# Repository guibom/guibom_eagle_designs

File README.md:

Miscellaneous OSH Stuff
====================

Misc breakouts, boards and parts for Cad Eagle.
All OSH with the MIT license.

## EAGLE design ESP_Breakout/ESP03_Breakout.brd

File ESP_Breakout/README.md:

ESP8266 module 01 & 03 Breakout
====================

Simple breakout for either module 01 (dip dual-header) or 03 (smd with ceramic antenna). Works fine on a breadboard (but it takes up some space).
Breaks out the GPIOs, and RST is tied to the GPIO16 pin.

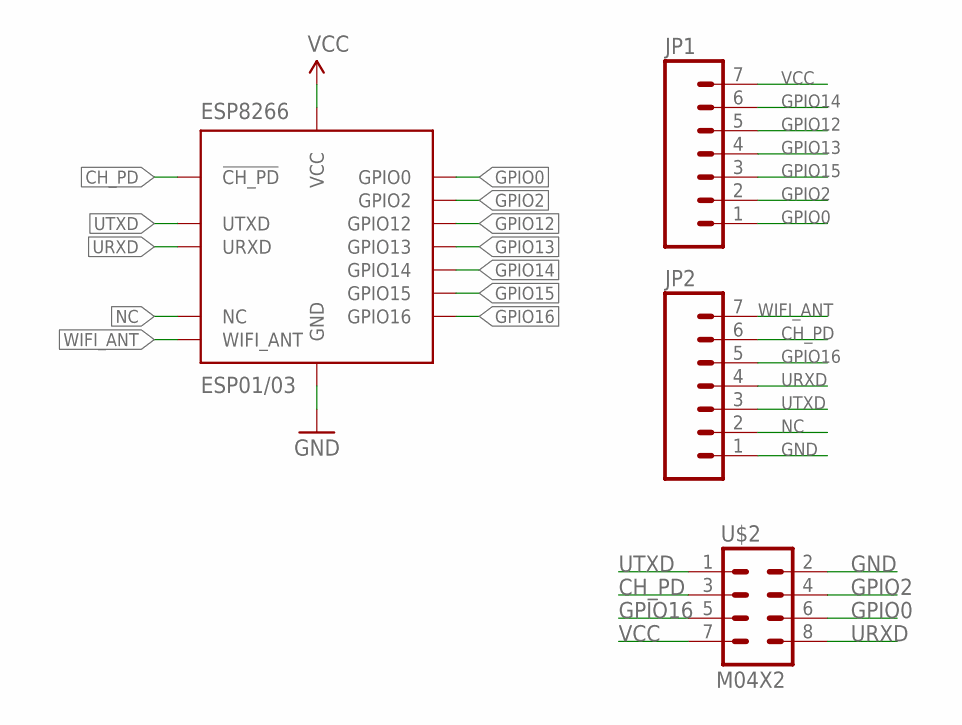
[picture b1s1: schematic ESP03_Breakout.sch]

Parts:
ESP8266: ESP01/03; ESP-03
JP1, JP2: M07; 1X07
U$2: M04X2; 2X4

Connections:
CH_PD: ESP8266.CH_PD (!CH_PD), JP2.6, U$2.3
GND: ESP8266.GND, JP2.1, U$2.2
GPIO0: ESP8266.GPIO0, JP1.1, U$2.6
GPIO2: ESP8266.GPIO2, JP1.2, U$2.4
GPIO12: ESP8266.GPIO12, JP1.5
GPIO13: ESP8266.GPIO13, JP1.4
GPIO14: ESP8266.GPIO14, JP1.6
GPIO15: ESP8266.GPIO15, JP1.3
GPIO16: ESP8266.GPIO16, JP2.5, U$2.5
NC: ESP8266.NC, JP2.2
URXD: ESP8266.URXD, JP2.4, U$2.8
UTXD: ESP8266.UTXD, JP2.3, U$2.1
VCC: ESP8266.VCC, JP1.7, U$2.7
WIFI_ANT: ESP8266.WIFI_ANT, JP2.7

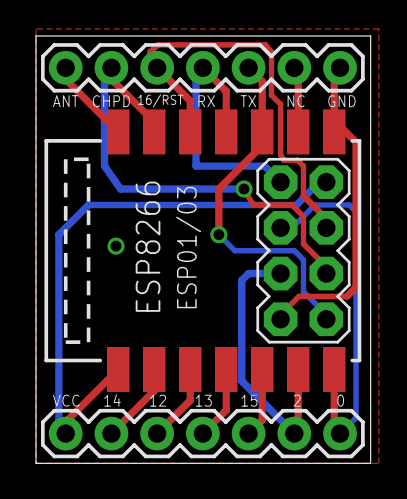
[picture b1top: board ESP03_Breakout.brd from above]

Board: 2 copper layers, 18.6 x 23.7 mm, 5 parts (1 on the bottom side), 14 nets.

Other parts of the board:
U$1: OSHW-LOGO-L

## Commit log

2014-10-26 Adding ESP 01/03 Breakout board Eagle files
2014-10-26 Adding readme
2014-10-26 Adding board render

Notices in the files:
parts and their libraries:
SparkFun-Connectors: Licensing: Creative Commons ShareAlike 4.0 International - https://creativecommons.org/licenses/by-sa/4.0
